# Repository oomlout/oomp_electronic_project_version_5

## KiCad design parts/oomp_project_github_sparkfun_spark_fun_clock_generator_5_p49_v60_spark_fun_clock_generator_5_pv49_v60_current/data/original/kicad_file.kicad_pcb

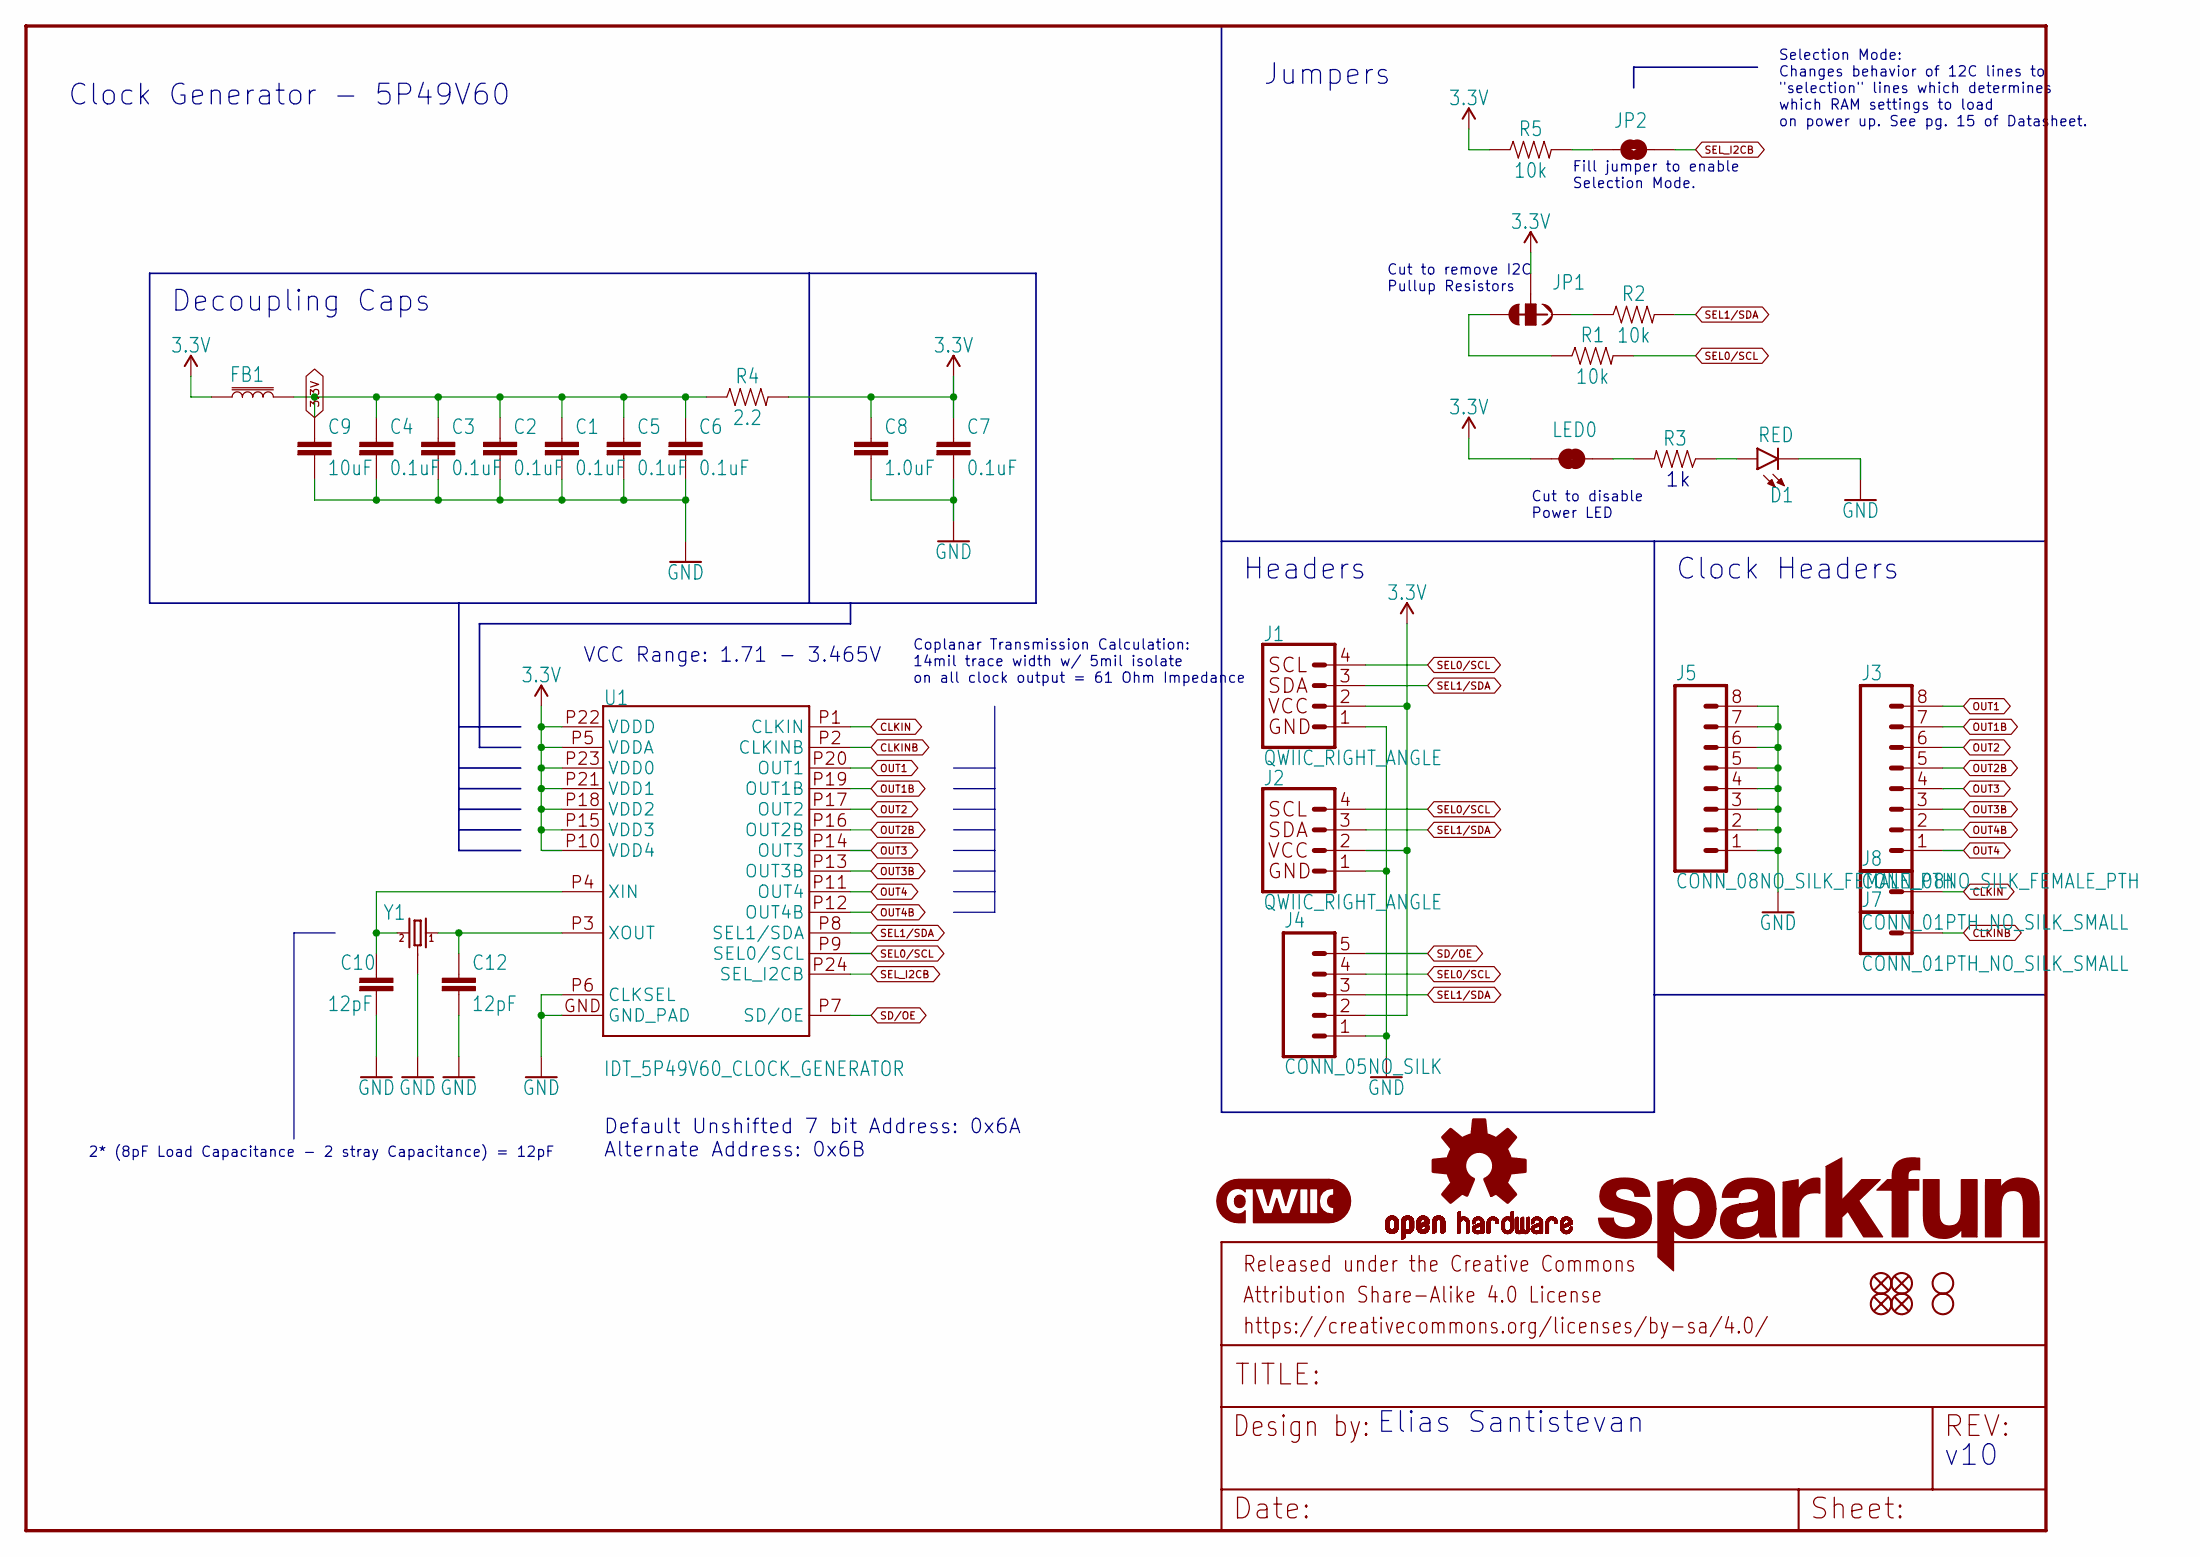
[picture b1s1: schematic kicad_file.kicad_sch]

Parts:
C1, C2, C3, C4, C5, C6, C7: 0.1uF; 0402
C8: 1.0uF; 0402
C9: 10uF; 0603
C10, C12: 12pF; 0402
D1: RED; LED-0603
FB1: FERRITE_BEAD-120_OHM-0402; 0402; MFG_PART BLM15HB121SN1D
FD1, FD2, FD3, FD4: FIDUCIALUFIDUCIAL; FIDUCIAL-MICRO
FRAME1: FRAME-LETTER; CREATIVE_COMMONS
H1, H2: STAND-OFFTIGHT; STAND-OFF-TIGHT
J1, J2: QWIIC_RIGHT_ANGLE; JST04_1MM_RA
J3, J5: CONN_08NO_SILK_FEMALE_PTH; 1X08_NO_SILK
J4: CONN_05NO_SILK; 1X05_NO_SILK
J7, J8: CONN_01PTH_NO_SILK_SMALL; 1X01_SMALL
JP1: JUMPER-SMT_3_2-NC_TRACE_SILK; SMT-JUMPER_3_2-NC_TRACE_SILK
JP2: JUMPER-SMT_2_NO_SILK; SMT-JUMPER_2_NO_SILK
LED0: JUMPER-SMT_2_NC_TRACE_SILK; SMT-JUMPER_2_NC_TRACE_SILK
LOGO1: SFE_LOGO_NAME.1_INCH; SFE_LOGO_NAME_.1
LOGO2: OSHW-LOGOS; OSHW-LOGO-S
LOGO3: QWIIC_LOGO_4MM; QWIIC_4MM
R1, R2, R5: 10k; 0402
R3: 1KOHM-0402-1/16W-1%; 0402
R4: 2.2; 0603
U1: IDT_5P49V60_CLOCK_GENERATOR; VFQFPN-24
Y1: 16MHz; CRYSTAL-SMD-2X2.5MM

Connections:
3.3V: C1.1, C2.1, C3.1, C4.1, C5.1, C6.1, C7.1, C8.1, C9.1, FB1.1, FB1.2, J1.2, J2.2, J4.2, JP1.2, LED0.2, R4.1, R4.2, R5.1, U1.P5 (VDDA), U1.P10 (VDD4), U1.P15 (VDD3), U1.P18 (VDD2), U1.P21 (VDD1), U1.P22 (VDDD), U1.P23 (VDD0)
CLKIN: J8.P$1, U1.P1 (CLKIN)
CLKINB: J7.P$1, U1.P2 (CLKINB)
GND: C1.2, C2.2, C3.2, C4.2, C5.2, C6.2, C7.2, C8.2, C9.2, C10.2, C12.2, D1.C, J1.1, J2.1, J4.1, J5.1, J5.2, J5.3, J5.4, J5.5, J5.6, J5.7, J5.8, U1.GND (GND_PAD), U1.P6 (CLKSEL), Y1.P2 (GND), Y1.P4 (GND)
unnamed: JP1.1, R2.1
unnamed: C12.1, U1.P3 (XOUT), Y1.P1 (1)
unnamed: JP1.3, R1.1
unnamed: LED0.1, R3.2
unnamed: D1.A, R3.1
unnamed: C10.1, U1.P4 (XIN), Y1.P3 (2)
unnamed: JP2.1, R5.2
OUT1: J3.8, U1.P20 (OUT1)
OUT1B: J3.7, U1.P19 (OUT1B)
OUT2: J3.6, U1.P17 (OUT2)
OUT2B: J3.5, U1.P16 (OUT2B)
OUT3: J3.4, U1.P14 (OUT3)
OUT3B: J3.3, U1.P13 (OUT3B)
OUT4: J3.1, U1.P11 (OUT4)
OUT4B: J3.2, U1.P12 (OUT4B)
SD/OE: J4.5, U1.P7 (SD/OE)
SEL0/SCL: J1.4, J2.4, J4.4, R1.2, U1.P9 (SEL0/SCL)
SEL1/SDA: J1.3, J2.3, J4.3, R2.2, U1.P8 (SEL1/SDA)
SEL_I2CB: JP2.2, U1.P24 (SEL_I2CB)

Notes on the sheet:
Selection Mode: Changes behavior of 12C lines to "selection" lines which determines which RAM settings to load on power up. See pg. 15 of Datasheet.
Headers
Default Unshifted 7 bit Address: 0x6A Alternate Address: 0x6B
Jumpers
Clock Headers
Cut to disable Power LED
Cut to remove I2C Pullup Resistors
Decoupling Caps
Coplanar Transmission Calculation: 14mil trace width w/ 5mil isolate on all clock output = 61 Ohm Impedance
v10
2* (8pF Load Capacitance - 2 stray Capacitance) = 12pF
Elias Santistevan
Fill jumper to enable Selection Mode.
Clock Generator - 5P49V60
VCC Range: 1.71 - 3.465V

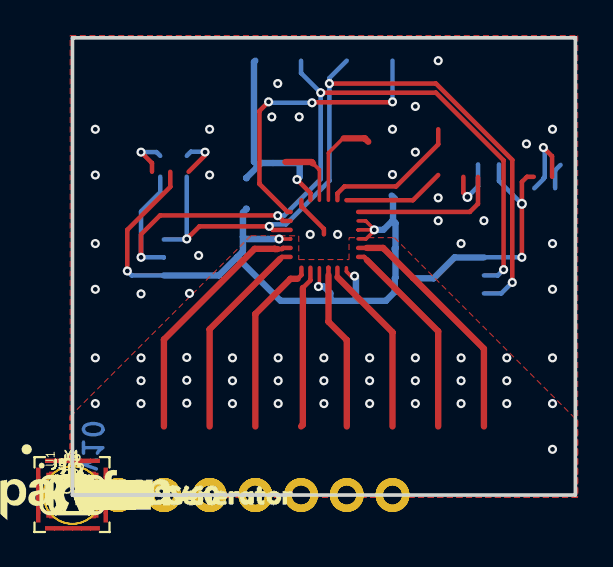
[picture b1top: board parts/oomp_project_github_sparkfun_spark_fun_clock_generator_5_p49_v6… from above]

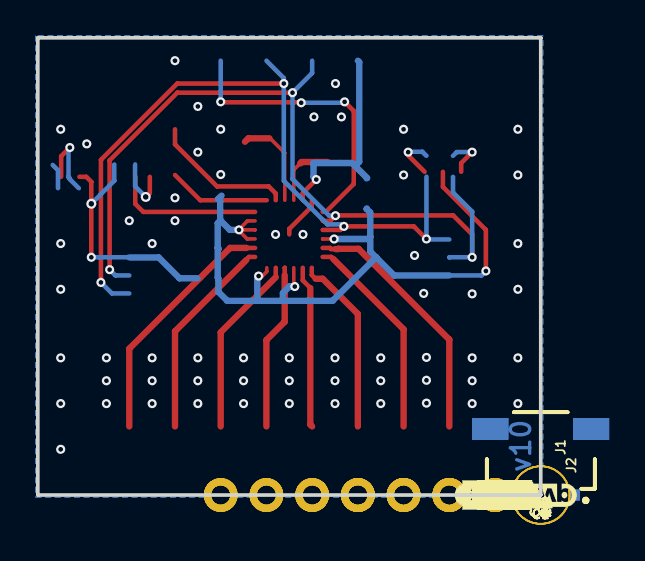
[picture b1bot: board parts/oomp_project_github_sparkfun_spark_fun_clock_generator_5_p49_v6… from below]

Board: 2 copper layers, 27.9 x 25.4 mm, 78 parts (38 on the bottom side), 23 nets.

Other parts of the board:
U$1: SEL0
U$2, U$18: 3V3-03
U$3, U$19: GND-03
U$4: PWR-()-03
U$5: SDA11
U$6: SCL10
U$7: SD#OE12
U$8, U$38: 46
U$9, U$25: 4B7
U$10, U$24: 3B5
U$11, U$37: 34
U$12, U$23: 2B3
U$13, U$27: 22
U$14, U$22: 1B1
U$15, U$26: 10
U$16: CLOCK_GENERATOR0
U$17: 5PV49V601
U$20, U$21: GND-04
U$28: SCL1
U$29: SD#OE2
U$30: SDA0
U$31, U$33: CLK12
U$32, U$34: CLKB13
U$35: I_SUPER2_C-()-03
U$36: LED0

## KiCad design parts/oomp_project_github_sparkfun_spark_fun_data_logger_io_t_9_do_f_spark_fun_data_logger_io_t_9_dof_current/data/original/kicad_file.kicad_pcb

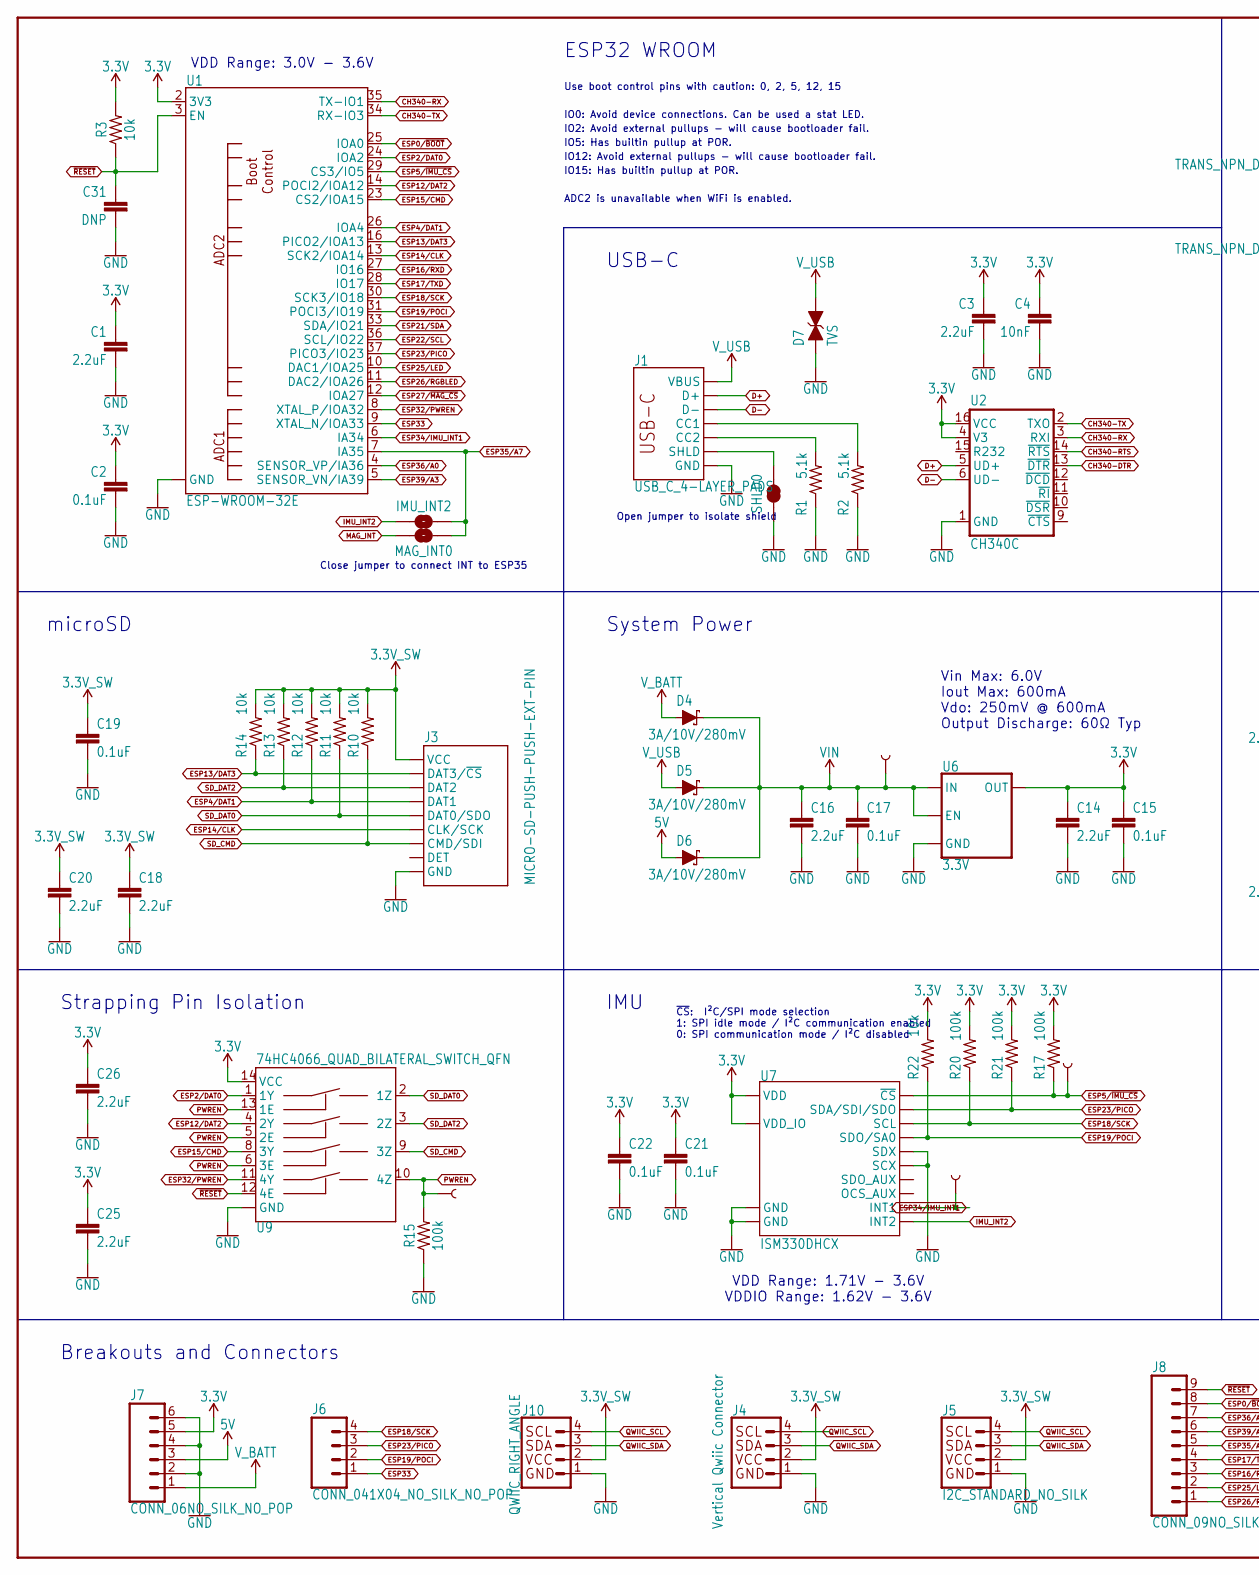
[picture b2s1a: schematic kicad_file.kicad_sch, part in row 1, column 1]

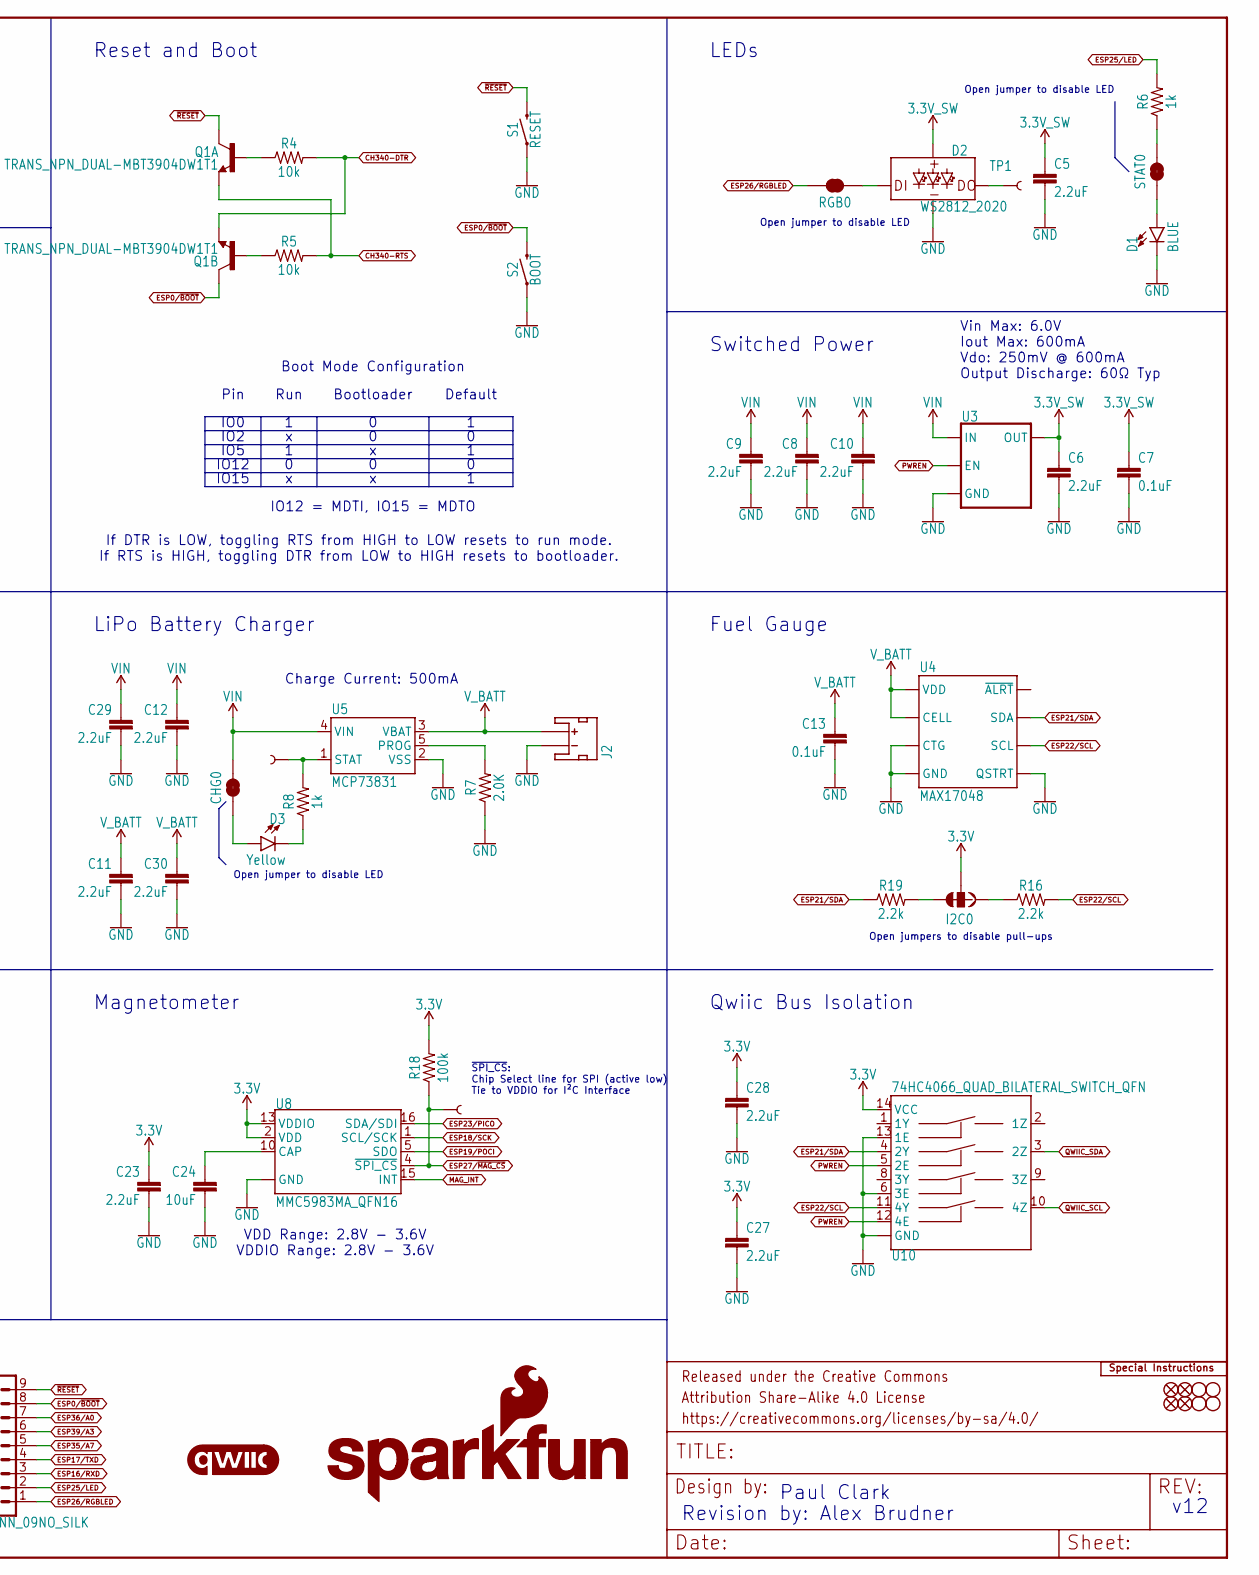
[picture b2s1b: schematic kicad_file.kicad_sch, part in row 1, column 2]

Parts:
C1, C3, C5, C6, C8, C9, C10, C11, C12, C14, C16, C18, C20, C23, C25, C26, C27, C28, C29, C30: 2.2uF; 0402-TIGHT
C2, C7, C13, C15, C17, C19, C21, C22: 0.1uF; 0402-TIGHT
C4: 10nF; 0402-TIGHT
C24: 10uF; 0402-TIGHT
C31: DNP; 0402-TIGHT_NO_CREAM
CHG0: JUMPER-SMT_2_NC_TRACE_SILK; SMT-JUMPER_2_NC_TRACE_SILK
D1: BLUE; LED-0603
D2: WS2812_2020; WS2812-2020
D3: Yellow; LED-0603
D4, D5, D6: 3A/10V/280mV; SOD-323
D7: TVS; 0603
FD1, FD2, FD3, FD4: FIDUCIAL1X2; FIDUCIAL-1X2
FRAME1: FRAME-LEDGER; CREATIVE_COMMONS
H1, H2, H3, H4: STAND-OFFTIGHT; STAND-OFF-TIGHT
I2C0: JUMPER-SMT_3_2-NC_TRACE_SILK; SMT-JUMPER_3_2-NC_TRACE_SILK
IMU_!CS!0: TEST-POINT3X5; PAD.03X.05
IMU_INT1: TEST-POINT3X5; PAD.03X.05
IMU_INT2: JUMPER-SMT_2_NO_SILK; SMT-JUMPER_2_NO_SILK
J1: USB_C_4-LAYER_PADS; USB-C-16P_4LAYER-PADS
J2: JST_2MM_MALE; JST-2-SMD
J3: MICRO-SD-PUSH-PUSH-EXT-PIN; MICROSD-EXTERNALPIN
J4: Vertical Qwiic Connector; JST04_1MM_VERT
J5: I2C_STANDARD_NO_SILK; 1X04_NO_SILK
J6: CONN_041X04_NO_SILK_NO_POP; 1X04_NO_SILK
J7: CONN_06NO_SILK_NO_POP; 1X06_NO_SILK
J8: CONN_09NO_SILK; 1X09_NO_SILK
J10: QWIIC_RIGHT_ANGLE; JST04_1MM_RA
LOGO1: SPECIAL_INSTRUCTIONS-ORDERING; ORDERING_INSTRUCTIONS
LOGO3: QWIIC_LOGO_6MM; QWIIC_6MM
LOGO5: SFE_LOGO_NAME.2_INCH; SFE_LOGO_NAME_.2
LOGO6: SFE_LOGO_FLAME.2_INCH; SFE_LOGO_FLAME_.2
MAG_!CS!0: TEST-POINT3X5; PAD.03X.05
MAG_INT0: JUMPER-SMT_2_NO_SILK; SMT-JUMPER_2_NO_SILK
PWREN0: TEST-POINT3X5; PAD.03X.05
Q1: TRANS_NPN_DUAL-MBT3904DW1T1; SC70-6
R1, R2: 5.1k; 0402-TIGHT
R3, R4, R5, R10, R11, R12, R13, R14, R22: 10k; 0402-TIGHT
R6, R8: 1k; 0402-TIGHT
R7: 2.0K; 0402-TIGHT
R15, R17, R18, R20, R21: 100k; 0402-TIGHT
R16, R19: 2.2k; 0402-TIGHT
RGB0: JUMPER-SMT_2_NC_TRACE_SILK; SMT-JUMPER_2_NC_TRACE_SILK
S1: RESET; TACTILE_SWITCH_SMD_RIGHT_ANGLE
S2: BOOT; TACTILE_SWITCH_SMD_RIGHT_ANGLE
SHLD0: JUMPER-SMT_2_NC_TRACE_SILK; SMT-JUMPER_2_NC_TRACE_SILK
STAT0: JUMPER-SMT_2_NC_TRACE_SILK; SMT-JUMPER_2_NC_TRACE_SILK
TP1: TEST-POINT3X5; PAD.03X.05
U1: ESP-WROOM-32E; ESP-WROOM-32D-NARROW
U2: CH340C; SO016
U3, U6: 3.3V; SOT23-5
U4: MAX17048; DFN-8
U5: MCP73831; SOT23-5
U7: ISM330DHCX; LGA-14L
U8: MMC5983MA_QFN16; LGA-16-3X3MM-4X4PINS
U9, U10: 74HC4066_QUAD_BILATERAL_SWITCH_QFN; 14-QFN
VIN0, VIN1: TEST-POINT3X5; PAD.03X.05

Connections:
3.3V: C1.1, C2.1, C3.1, C4.1, C14.1, C15.1, C21.1, C22.1, C23.1, C25.1, C26.1, C27.1, C28.1, I2C0.2, J7.5, R3.2, R17.2, R18.2, R20.2, R21.2, R22.2, U1.2 (3V3), U2.4 (V3), U2.16 (VCC), U6.5 (OUT), U7.P5 (VDD_IO), U7.P8 (VDD), U8.2 (VDD), U8.13 (VDDIO), U9.14 (VCC), U10.14 (VCC)
3.3V_SW: C5.1, C6.1, C7.1, C18.1, C19.1, C20.1, D2.VCC, J3.4 (VCC), J4.2, J5.2, J10.2, R10.2, R11.2, R12.2, R13.2, R14.2, U3.5 (OUT)
5V: D6.A, J7.3
CAP: C24.1, U8.10 (CAP)
CH340-DTR: Q1.1 (E), R4.2, U2.13 (~DTR)
CH340-RTS: Q1.4 (E), R5.2, U2.14 (~RTS)
CH340-RX: U1.35 (TX-IO1), U2.3 (RXI)
CH340-TX: U1.34 (RX-IO3), U2.2 (TXO)
D+: J1.A6 (D+), J1.B6 (D+), U2.5 (UD+)
D-: J1.A7 (D-), J1.B7 (D-), U2.6 (UD-)
ESP0/~BOOT: J8.8, Q1.6 (C), S2.2, U1.25 (IOA0)
ESP2/DAT0: U1.24 (IOA2), U9.1 (1Y)
ESP4/DAT1: J3.8 (DAT1), R12.1, U1.26 (IOA4)
ESP5/~IMU_CS: IMU_!CS!0.1, R17.1, U1.29 (CS3/IO5), U7.P12 (~CS)
ESP12/DAT2: U1.14 (POCI2/IOA12), U9.4 (2Y)
ESP13/DAT3: J3.2 (DAT3/~CS), R14.1, U1.16 (PICO2/IOA13)
ESP14/CLK: J3.5 (CLK/SCK), U1.13 (SCK2/IOA14)
ESP15/CMD: U1.23 (CS2/IOA15), U9.8 (3Y)
ESP16/RXD: J8.3, U1.27 (IO16)
ESP17/TXD: J8.4, U1.28 (IO17)
ESP18/SCK: J6.4, R20.1, U1.30 (SCK3/IO18), U7.P13 (SCL), U8.1 (SCL/SCK)
ESP19/POCI: J6.2, R22.1, U1.31 (POCI3/IO19), U7.P1 (SDO/SA0), U8.5 (SDO)
ESP21/SDA: R19.1, U1.33 (SDA/IO21), U4.8 (SDA), U10.4 (2Y)
ESP22/SCL: R16.2, U1.36 (SCL/IO22), U4.7 (SCL), U10.11 (4Y)
ESP23/PICO: J6.3, R21.1, U1.37 (PICO3/IO23), U7.P14 (SDA/SDI/SDO), U8.16 (SDA/SDI)
ESP25/LED: J8.2, R6.2, U1.10 (DAC1/IOA25)
ESP26/RGBLED: J8.1, RGB0.2, U1.11 (DAC2/IOA26)
ESP27/~MAG_CS: MAG_!CS!0.1, R18.1, U1.12 (IOA27), U8.4 (~SPI_CS)
ESP32/PWREN: U1.8 (XTAL_P/IOA32), U9.11 (4Y)
ESP33: J6.1, U1.9 (XTAL_N/IOA33)
ESP34/IMU_INT1: IMU_INT1.1, U1.6 (IA34), U7.P4 (INT1)
ESP35/A7: IMU_INT2.2, J8.5, MAG_INT0.2, U1.7 (IA35)
ESP36/A0: J8.7, U1.4 (SENSOR_VP/IA36)
ESP39/A3: J8.6, U1.5 (SENSOR_VN/IA39)
GND: C1.2, C2.2, C3.2, C4.2, C5.2, C6.2, C7.2, C8.2, C9.2, C10.2, C11.2, C12.2, C13.2, C14.2, C15.2, C16.2, C17.2, C18.2, C19.2, C20.2, C21.2, C22.2, C23.2, C24.2, C25.2, C26.2, C27.2, C28.2, C29.2, C30.2, C31.2, D1.C, D2.GND, D7.1 (A), J1.GND, J1.GND2 (GND), J2.1 (-), J3.6 (GND), J3.10 (GND), J3.11 (GND), J3.12 (GND), J3.13 (GND), J4.1, J5.1, J7.2, J7.4, J7.6, J10.1, R1.1, R2.1, R7.1, R15.1, S1.1, S2.1, SHLD0.1, U1.1 (GND), U1.15 (GND), U1.38 (GND), U1.GND1 (GND), U1.GNDT1 (GND), U1.GNDT2 (GND), U1.GNDT3 (GND), U1.GNDT4 (GND), U1.GNDT5 (GND), U1.GNDT6 (GND), U1.GNDT7 (GND), U1.GNDT8 (GND), U2.1 (GND), U3.2 (GND), U4.1 (CTG), U4.4 (GND), U4.6 (QSTRT), U4.9 (GND), U5.2 (VSS), U6.2 (GND), U7.P2 (SDX), U7.P3 (SCX), U7.P6 (GND), U7.P7 (GND), U8.9 (GND), U8.11 (GND), U9.7 (GND), U9.EPAD (GND), U10.6 (3E), U10.7 (GND), U10.13 (1E), U10.EPAD (GND)
IMU_INT2: IMU_INT2.1, U7.P9 (INT2)
MAG_INT: MAG_INT0.1, U8.15 (INT)
unnamed: J1.B5 (CC2), R1.2
unnamed: J1.A5 (CC1), R2.2
unnamed: Q1.2 (B), R5.1
unnamed: Q1.5 (B), R4.1
unnamed: R6.1, STAT0.2
unnamed: D2.DO, TP1.1
unnamed: CHG0.1, D3.A
unnamed: D3.C, R8.1
unnamed: R8.2, U5.1 (STAT), VIN1.1
unnamed: R7.2, U5.5 (PROG)
unnamed: D2.DI, RGB0.1
unnamed: D1.A, STAT0.1
unnamed: I2C0.1, R16.1
unnamed: I2C0.3, R19.2
PWREN: PWREN0.1, R15.2, U3.3 (EN), U9.5 (2E), U9.6 (3E), U9.10 (4Z), U9.13 (1E), U10.5 (2E), U10.12 (4E)
QWIIC_SCL: J4.4, J5.4, J10.4, U10.10 (4Z)
QWIIC_SDA: J4.3, J5.3, J10.3, U10.3 (2Z)
SD_CMD: J3.3 (CMD/SDI), R10.1, U9.9 (3Z)
SD_DAT0: J3.7 (DAT0/SDO), R11.1, U9.2 (1Z)
SD_DAT2: J3.1 (DAT2), R13.1, U9.3 (2Z)
SHIELD: J1.SHLD1 (SHLD), J1.SHLD2 (SHLD), J1.SHLD3 (SHLD), J1.SHLD4 (SHLD), SHLD0.2
VIN: C8.1, C9.1, C10.1, C12.1, C16.1, C17.1, C29.1, CHG0.2, D4.C, D5.C, D6.C, U3.1 (IN), U5.4 (VIN), U6.1 (IN), U6.3 (EN), VIN0.1
V_BATT: C11.1, C13.1, C30.1, D4.A, J2.2 (+), J7.1, U4.2 (CELL), U4.3 (VDD), U5.3 (VBAT)
V_USB: D5.A, D7.2 (C), J1.VBUS1 (VBUS), J1.VBUS2 (VBUS)
~RESET: C31.1, J8.9, Q1.3 (C), R3.1, S1.2, U1.3 (EN), U9.12 (4E)

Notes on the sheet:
IO12 = MDTI, IO15 = MDTO
IO2
Paul Clark
VDD Range: 2.8V - 3.6V VDDIO Range: 2.8V - 3.6V
IO15: Has builtin pullup at POR.
LEDs
VDD Range: 3.0V - 3.6V
Pin
If DTR is LOW, toggling RTS from HIGH to LOW resets to run mode. If RTS is HIGH, toggling DTR from LOW to HIGH resets to bootloader.
Fuel Gauge
Vin Max: 6.0V Iout Max: 600mA Vdo: 250mV @ 600mA Output Discharge: 60Ω Typ
IO0: Avoid device connections. Can be used a stat LED.
~{CS}: I²C/SPI mode selection 1: SPI idle mode / I²C communication enabled 0: SPI communication mode / I²C disabled
Qwiic Bus Isolation
microSD
IO2: Avoid external pullups - will cause bootloader fail.
Open jumper to isolate shield
Charge Current: 500mA
IO0
Run
Open jumper to disable LED
Strapping Pin Isolation
LiPo Battery Charger
IO5
System Power
Revision by: Alex Brudner
VDD Range: 1.71V - 3.6V VDDIO Range: 1.62V - 3.6V
~{SPI_CS}: Chip Select line for SPI (active low) Tie to VDDIO for I²C Interface
Boot Mode Configuration
Switched Power
ADC2 is unavailable when WiFi is enabled.
IMU
IO12: Avoid external pullups - will cause bootloader fail.
IO15
IO12
USB-C
Use boot control pins with caution: 0, 2, 5, 12, 15
ESP32 WROOM
Magnetometer
Breakouts and Connectors

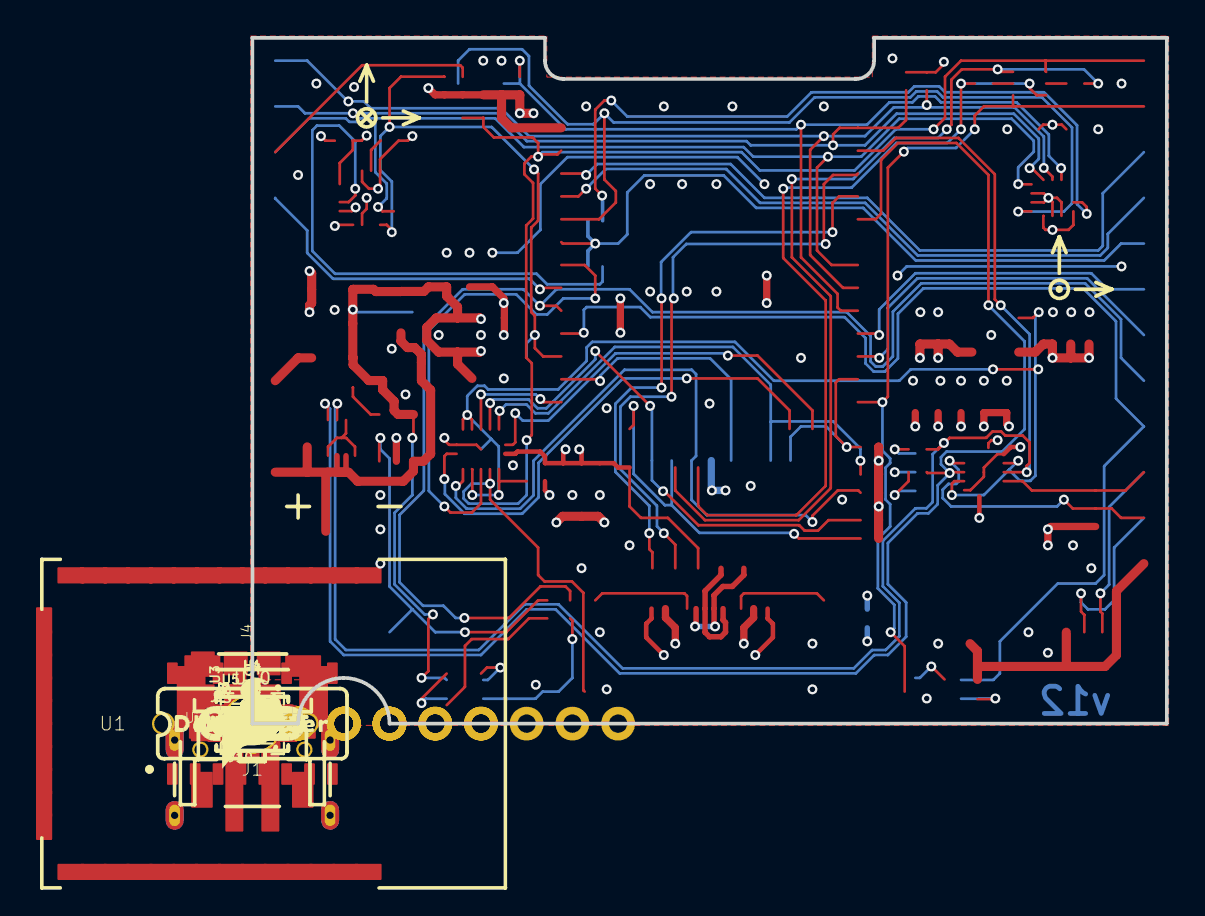
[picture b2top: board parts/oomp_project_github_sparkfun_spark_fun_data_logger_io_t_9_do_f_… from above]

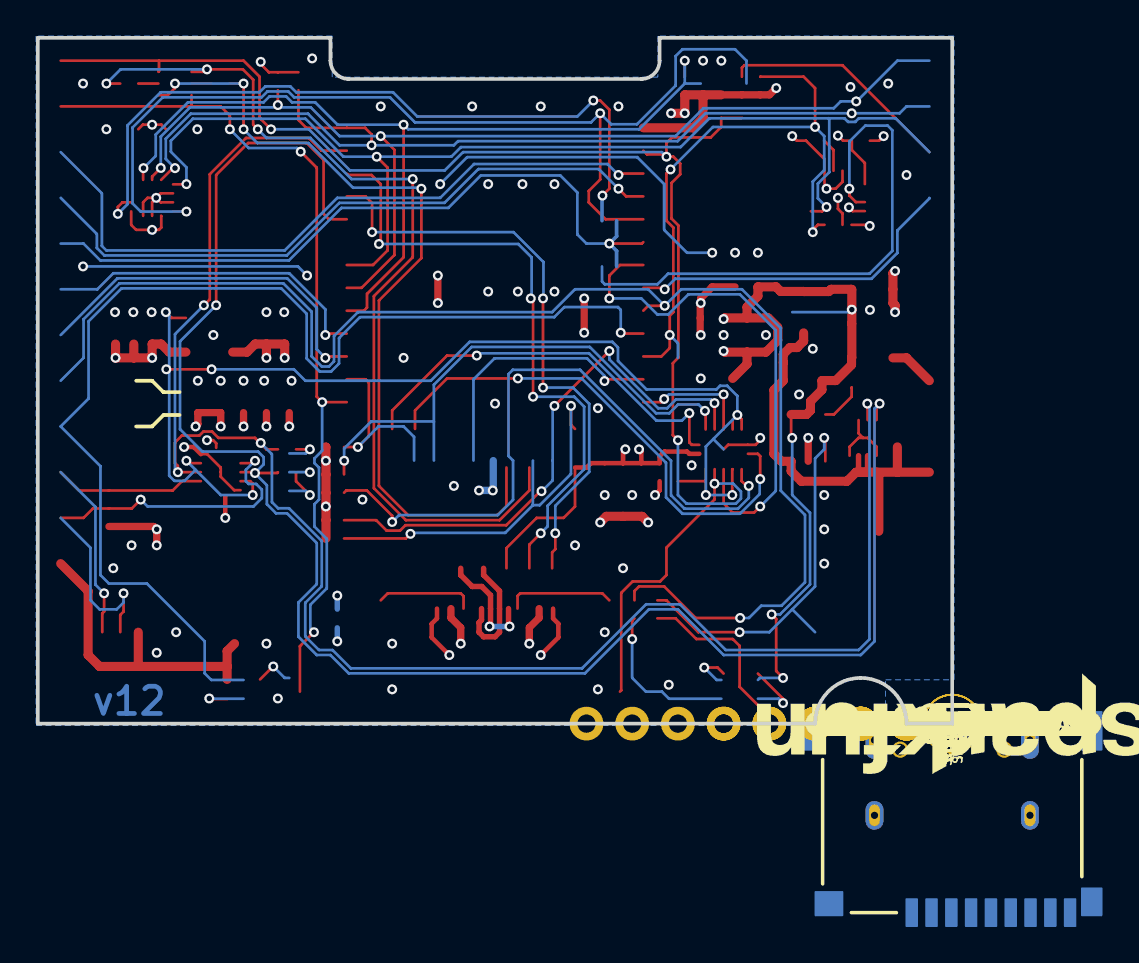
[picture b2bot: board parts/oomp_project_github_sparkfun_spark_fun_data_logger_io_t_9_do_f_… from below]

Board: 4 copper layers, 50.8 x 38.1 mm, 158 parts (54 on the bottom side), 62 nets.

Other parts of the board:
U$1: IOT_9DOF0
U$2: RESET0
U$3, U$6: STAT0
U$4, U$5: CHG0
U$7: 0_#_BOOT0
U$8: IMU0
U$9: MAG0
U$10, U$13: X0
U$11, U$14: Y0
U$12, U$15: Z0
U$16: ##RESET##0
U$17: #0_#_#BOOT##0
U$18: #36_#_A0#0
U$19: #39_#_A3#0
U$20: #35_#_A7#0
U$21: #17_#_TXD#0
U$22: #16_#_RXD#0
U$23: #25#0
U$24: #26#0
U$25: #SCL#0
U$26: #SDA#0
U$27: #3V3_SW#0
U$28: #GND#0
U$29, U$30, U$31: #GND#1
U$32: #BATT#0
U$33: #5V#0
U$34: #3V3#0
U$35: #33#0
U$36: #POCI_#_19#0
U$37: #PICO_#_23#0
U$38: #SCK_#_18#0
U$40: #IMU_INT2#0
U$41: #MAG_INT#0
U$42, U$43: #35#0
U$44: IOT_9DOF10
U$45: #SHLD#0
U$46: #I�C#0
U$47: STAT_LED0
U$48: RGB_LED0
U$49: RGB0
U$50: DATALOGGER0
U$51: DATALOGGER1

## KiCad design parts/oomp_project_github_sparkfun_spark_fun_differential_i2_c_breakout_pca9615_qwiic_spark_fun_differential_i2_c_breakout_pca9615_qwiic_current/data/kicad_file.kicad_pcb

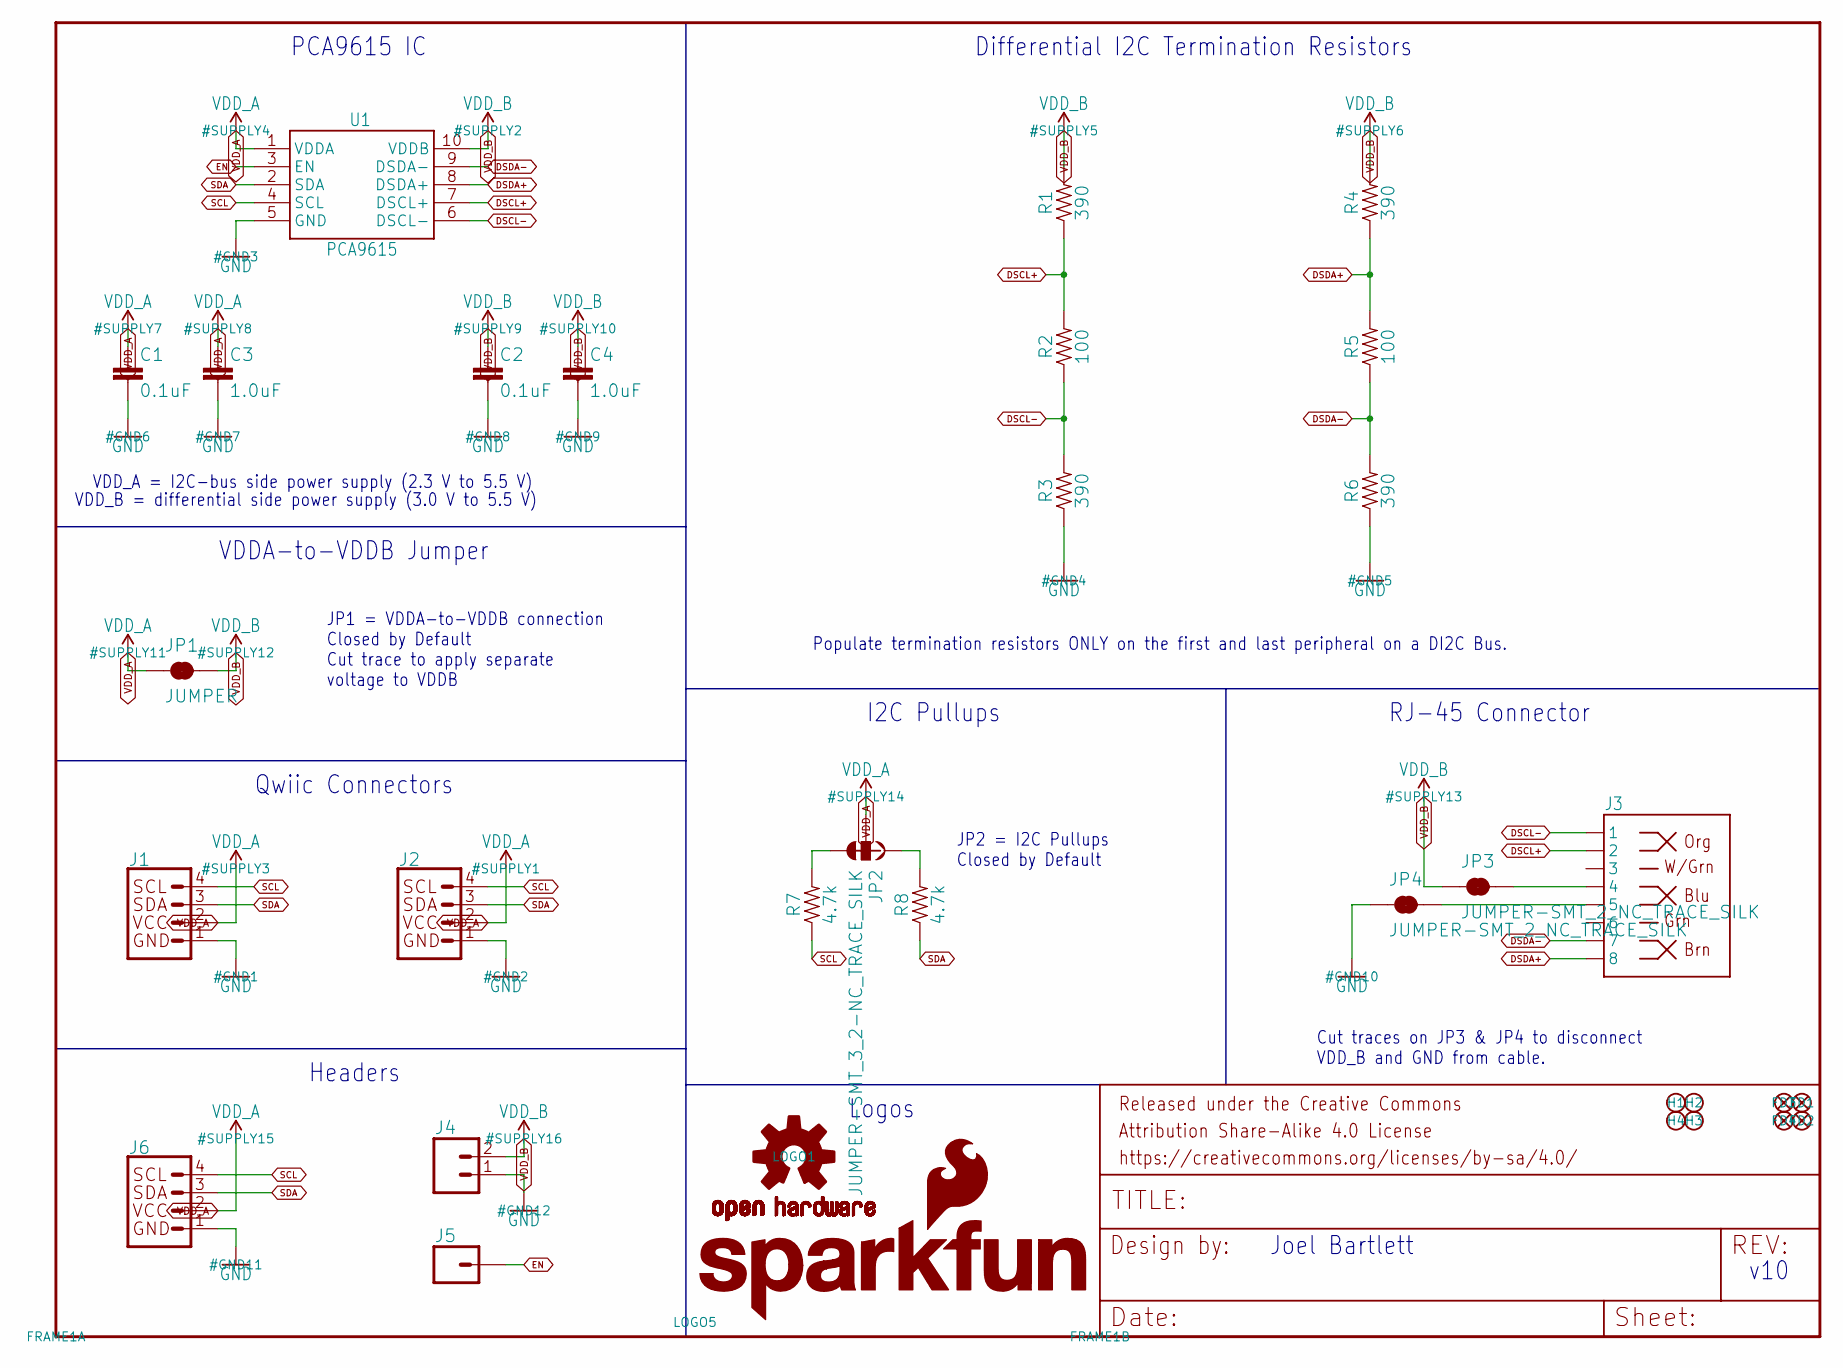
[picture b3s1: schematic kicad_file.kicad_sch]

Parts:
C1, C2: 0.1uF; 0603
C3, C4: 1.0uF; 0603
FD1, FD2, FD3, FD4: FIDUCIALUFIDUCIAL; FIDUCIAL-MICRO
FRAME1: FRAME-LETTER; CREATIVE_COMMONS
H1, H2, H3, H4: STAND-OFF
J1, J2: QWIIC_CONNECTORJS-1MM; 1X04_1MM_RA
J3: RJ45; RJ45-8
J4: CONN_021X02_NO_SILK; 1X02_NO_SILK
J5: CONN_01PTH_NO_SILK_YES_STOP; 1X01_NO_SILK
J6: I2C_STANDARD_NO_SILK; 1X04_NO_SILK
JP1: JUMPER; SMT-JUMPER_2_NC_TRACE_SILK
JP2: JUMPER-SMT_3_2-NC_TRACE_SILK; SMT-JUMPER_3_2-NC_TRACE_SILK
JP3, JP4: JUMPER-SMT_2_NC_TRACE_SILK; SMT-JUMPER_2_NC_TRACE_SILK
LOGO1: OSHW-LOGOM; OSHW-LOGO-M
LOGO5: SFE_LOGO_NAME_FLAME.1_INCH; SFE_LOGO_NAME_FLAME_.1
R1, R3, R4, R6: 390; 0603
R2, R5: 100; 0603
R7, R8: 4.7k; 0603
U1: PCA9615; TSSOP10

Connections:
DSCL+: J3.2, R1.1, R2.2, U1.7 (DSCL+)
DSCL-: J3.1, R2.1, R3.2, U1.6 (DSCL-)
DSDA+: J3.8, R4.1, R5.2, U1.8 (DSDA+)
DSDA-: J3.7, R5.1, R6.2, U1.9 (DSDA-)
EN: J5.1, U1.3 (EN)
GND: C1.2, C2.2, C3.2, C4.2, J1.1, J2.1, J4.1, J6.1 (GND), JP4.1, R3.1, R6.1, U1.5 (GND)
unnamed: J3.4, JP3.2
unnamed: J3.5, JP4.2
unnamed: JP2.1, R8.2
unnamed: JP2.3, R7.2
SCL: J1.4, J2.4, J6.4 (SCL), R7.1, U1.4 (SCL)
SDA: J1.3, J2.3, J6.3 (SDA), R8.1, U1.2 (SDA)
VDD_A: C1.1, C3.1, J1.2, J2.2, J6.2 (VCC), JP1.1, JP2.2, U1.1 (VDDA)
VDD_B: C2.1, C4.1, J4.2, JP1.2, JP3.1, R1.2, R4.2, U1.10 (VDDB)

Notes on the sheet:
RJ-45 Connector
Qwiic Connectors
VDD_B = differential side power supply (3.0 V to 5.5 V)
Populate termination resistors ONLY on the first and last peripheral on a DI2C Bus.
v10
JP1 = VDDA-to-VDDB connection Closed by Default Cut trace to apply separate voltage to VDDB
I2C Pullups
Headers
VDD_A = I2C-bus side power supply (2.3 V to 5.5 V)
PCA9615 IC
JP2 = I2C Pullups Closed by Default
Joel Bartlett
Logos
Cut traces on JP3 & JP4 to disconnect VDD_B and GND from cable.
Differential I2C Termination Resistors
VDDA-to-VDDB Jumper

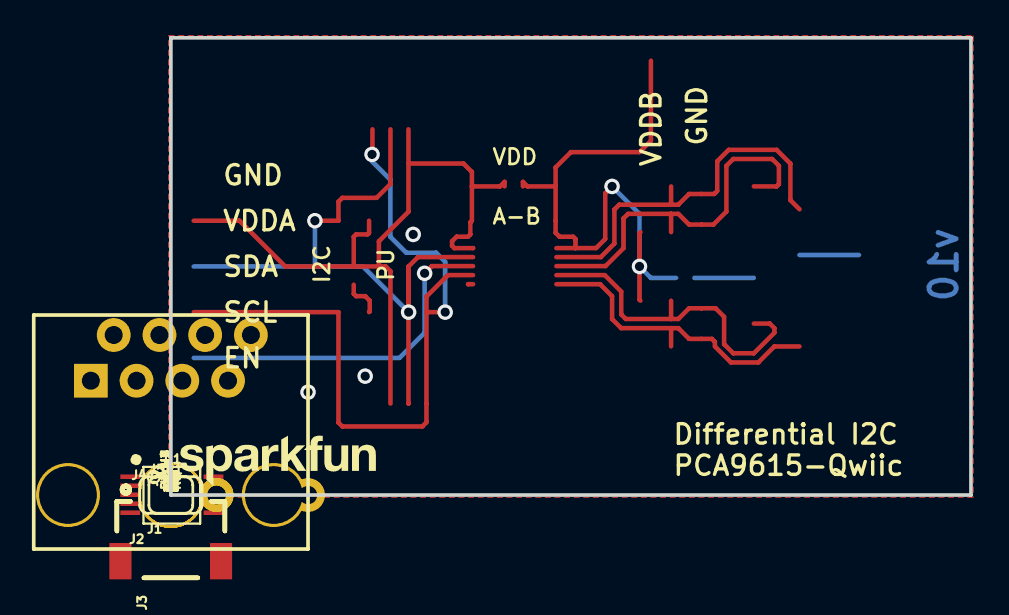
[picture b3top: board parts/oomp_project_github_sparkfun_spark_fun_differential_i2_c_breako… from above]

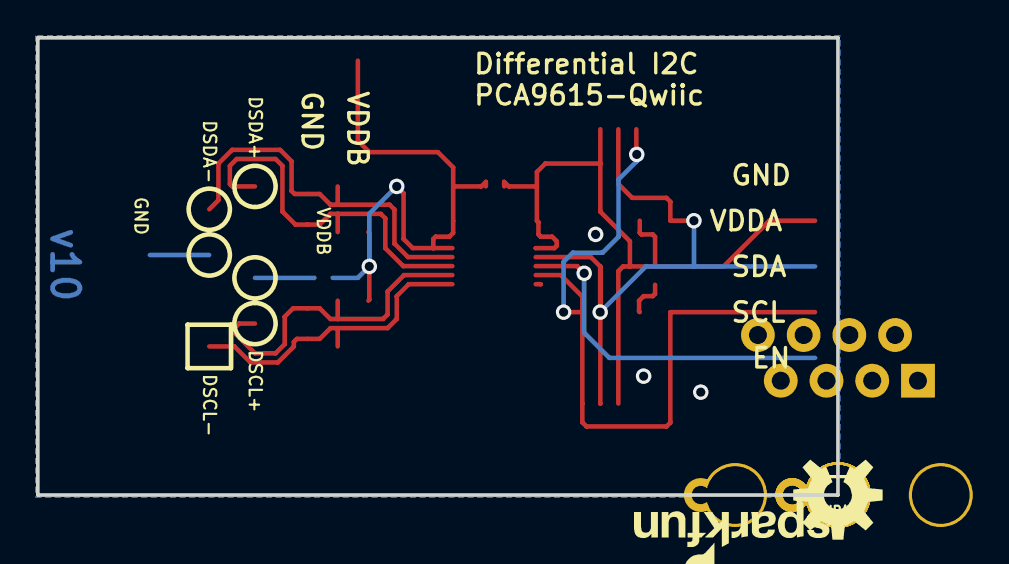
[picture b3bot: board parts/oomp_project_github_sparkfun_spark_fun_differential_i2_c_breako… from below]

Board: 2 copper layers, 44.5 x 25.4 mm, 35 parts (6 on the bottom side), 14 nets.

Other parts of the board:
LOGO3: SFE_LOGO_NAME.1_INCH; SFE_LOGO_NAME_.1

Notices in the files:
parts/oomp_project_github_sparkfun_spark_fun_clock_generator_5_p49_v60_spark_fun_clock_generator_5_pv49_v60_current/data/original/kicad_file.kicad_sch:
Released under the Creative Commons
https://creativecommons.org/licenses/by-sa/4.0
parts and their libraries:
Released under the Creative Commons Attribution Share-Alike 4.0 License
